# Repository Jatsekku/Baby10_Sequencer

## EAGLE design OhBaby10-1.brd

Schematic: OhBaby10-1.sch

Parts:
C1, C1S, C2, C2S, C3, C3S, C4, C4S, C5, C5S, C6, C6S, C7, C7S, C8, C8S, C9, C9S, C10, C10S, C11, C11S, C12, C12S, C20: C-EUC0805; C0805
C1P: CPOL-EU153CLV-0405; 153CLV-0405
C2P: C-EUC0805K; C0805K
C3P: 470nF; C0805
CV_OUT: JACK3.5; JACK_FANCY
D1P: SM4001; MELF-MLL41_DO213AB
DSA: CPOL-EU153CLV-0405; 153CLV-0405
EXT_CLK_IN, EXT_CLK_IN1: JACK3.5; JACK_FANCY
F1: FUSEB; 0805
IC1, IC2, IC3, IC4, IC5, IC6, IC7, IC8, IC9, IC10, IC11, IC12: TTP223-BA6; SOT95P285X126-6N
IC13, IC14, IC17: 74HC08D; SO14
IC15: 4017D; SO16
IC16: 74HC32D; SO14
IC18: IC_TD62783-SO-18W; SO-18L
IC19: NE555D; SO08
IC20: REG1117; SOT223
LED1, LED2, LED3, LED4, LED5, LED6, LED7, LED8, LED9, LED10, LED11, LED12: LED_3PIN; LED_3PIN_SMD
OUT_S1, OUT_S2, OUT_S3, OUT_S4, OUT_S5, OUT_S6, OUT_S7, OUT_S8: JACK3.5; JACK_FANCY
POT_S1, POT_S2, POT_S3, POT_S4, POT_S5, POT_S6, POT_S7, POT_S8: V_POT; POT_FANCY
POWER: IDC10; ML10
R1, R1Q, R2Q, R3Q, R3Q1, R4Q, R5Q, R8Q, R9Q: R-EU_R1206; R1206
R1L, R2L, R3L, R4L, R5L, R6L, R6Q, R7L, R7Q, R8L, R9L, R10L, R10Q, R11L, R12L: R-EU_R0805; R0805
TP1, TP2, TP3, TP4, TP5, TP6, TP7, TP8, TP10, TP11, TP12, TP13: TOUCH_PAD; TOUCH_PAD_8X8
U$1: JST_2MM_10P
U$2, U$7, U$8, U$9, U$10, U$11, U$12, U$13, U$14, U$15, U$16, U$17, U$18, U$19, U$20, U$21, U$23, U$24, U$25, U$26: SP_SMD; SINGLE_PAD_SMD
U$4: JST_2MM_9P
U$5: JST_2MM_2P
U$6: V_POT; POT_FANCY
U$22: JST_2MM_6P
Z1, Z2, Z8, Z9: R-EU_R1206; R1206
Z3, Z4, Z5, Z6, Z7, Z10: R-EU_R2010; R2010

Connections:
555_CLK: IC19.3 (Q), U$22.P$2 (2)
555_VCC: C20.1, IC19.4 (R), IC19.8 (V+), U$5.P$2 (2), Z9.1
4017_Q0: IC13.12 (I0), IC15.3 (Q0), R1Q.1
4017_Q1: IC13.1 (I0), IC15.2 (Q1), R2Q.1, U$4.P$8 (8)
4017_Q2: IC14.1 (I0), IC15.4 (Q2), R3Q.1, U$4.P$7 (7)
4017_Q3: IC15.7 (Q3), R4Q.1, U$4.P$4 (4), Z5.1
4017_Q4: IC13.9 (I0), IC15.10 (Q4), R5Q.1, U$4.P$3 (3)
4017_Q5: IC13.4 (I0), IC15.1 (Q5), R6Q.2, U$4.P$9 (9)
4017_Q6: IC14.4 (I0), IC15.5 (Q6), R7Q.2, U$4.P$6 (6)
4017_Q7: IC15.6 (Q7), R8Q.1, U$4.P$5 (5), Z4.1
4017_Q8: IC15.9 (Q8), U$4.P$2 (2)
+12V_PWR: D1P.C, F1.1, POWER.9, POWER.10
CLK_SUM: IC15.14 (CLK), IC16.6 (O), R10Q.1
GND: C1.2, C1P.-, C1S.2, C2.2, C2P.2, C2S.2, C3.2, C3P.2, C3S.2, C4.2, C4S.2, C5.2, C5S.2, C6.2, C6S.2, C7.2, C7S.2, C8.2, C8S.2, C9.2, C9S.2, C10.2, C10S.2, C11.2, C11S.2, C12.2, C12S.2, C20.2, D1P.A, DSA.-, IC1.2 (VSS), IC1.4 (AHLB), IC2.2 (VSS), IC2.4 (AHLB), IC3.2 (VSS), IC3.4 (AHLB), IC4.2 (VSS), IC4.4 (AHLB), IC5.2 (VSS), IC5.4 (AHLB), IC6.2 (VSS), IC6.4 (AHLB), IC7.2 (VSS), IC7.4 (AHLB), IC8.2 (VSS), IC8.4 (AHLB), IC9.2 (VSS), IC9.4 (AHLB), IC9.6 (TOG), IC10.2 (VSS), IC10.4 (AHLB), IC10.6 (TOG), IC11.2 (VSS), IC11.4 (AHLB), IC12.2 (VSS), IC12.4 (AHLB), IC13.7 (GND), IC14.7 (GND), IC15.8 (VSS), IC15.13 (ENA), IC16.7 (GND), IC17.7 (GND), IC18.10 (VS), IC19.1 (GND), IC20.1 (GND), LED1.P$1 (C), LED2.P$1 (C), LED3.P$1 (C), LED4.P$1 (C), LED5.P$1 (C), LED6.P$1 (C), LED7.P$1 (C), LED8.P$1 (C), LED9.P$1 (C), LED10.P$1 (C), LED11.P$1 (C), LED12.P$1 (C), POWER.3, POWER.4, POWER.5, POWER.6, POWER.7, POWER.8, R3Q1.1, R3Q1.2, U$1.P$9 (9), U$22.P$6 (6)
INT/EXT_CLK: IC17.4 (I0), U$22.P$4 (4)
INT/EXT_RST: IC17.1 (I0), U$22.P$3 (3)
KEY1: IC1.1 (Q), IC13.13 (I1), R1L.1
KEY2: IC2.1 (Q), IC13.2 (I1), R2L.1
KEY3: IC3.1 (Q), IC14.2 (I1), R3L.1
KEY4: IC4.1 (Q), R4L.1, Z7.1
KEY5: IC5.1 (Q), R5L.1, Z8.1
KEY6: IC6.1 (Q), IC13.5 (I1), R6L.1
KEY7: IC7.1 (Q), IC14.5 (I1), R7L.1
KEY8: IC8.1 (Q), R8L.1, Z6.1
KEY11: IC11.1 (Q), IC17.5 (I1), R11L.2
MAN_CLK: IC10.1 (Q), IC16.4 (I0), R10L.2
MAN_RST: IC9.1 (Q), IC16.1 (I0), R9L.2
unnamed: DSA.+, IC19.2 (TR), IC19.6 (THR), R1.1
unnamed: C10S.1, IC10.3 (I), TP11.P$1
unnamed: IC19.7 (DIS), R1.2, U$5.P$1 (1)
unnamed: LED9.P$2 (AR), R10L.1
unnamed: C1S.1, IC1.3 (I), TP1.P$1
unnamed: C11S.1, IC11.3 (I), TP12.P$1
unnamed: LED12.P$2 (AR), R11L.1
unnamed: C9S.1, IC9.3 (I), TP13.P$1
unnamed: LED1.P$2 (AR), R1Q.2
unnamed: C5S.1, IC5.3 (I), TP5.P$1
unnamed: IC16.5 (I1), U$26.P$1
unnamed: LED10.P$2 (AR), R9L.1
unnamed: LED1.P$3 (AG), R1L.2
unnamed: LED2.P$2 (AR), R2Q.2
unnamed: LED9.P$3 (AG), R10Q.2
unnamed: LED2.P$3 (AG), R2L.2
unnamed: C2S.1, IC2.3 (I), TP2.P$1
unnamed: IC16.2 (I1), U$23.P$1
unnamed: LED3.P$2 (AR), R3Q.2
unnamed: LED3.P$3 (AG), R3L.2
unnamed: C12S.1, IC12.3 (I), TP10.P$1
unnamed: LED4.P$2 (AR), R4Q.2
unnamed: LED11.P$2 (AR), R12L.1
unnamed: LED4.P$3 (AG), R4L.2
unnamed: LED5.P$2 (AR), R5Q.2
unnamed: C3S.1, IC3.3 (I), TP3.P$1
unnamed: LED5.P$3 (AG), R5L.2
unnamed: LED6.P$2 (AR), R6Q.1
unnamed: LED6.P$3 (AG), R6L.2
unnamed: LED7.P$2 (AR), R7Q.1
unnamed: C4S.1, IC4.3 (I), TP4.P$1
unnamed: LED7.P$3 (AG), R7L.2
unnamed: LED8.P$2 (AR), R8Q.2
unnamed: IC17.3 (O), U$24.P$1
unnamed: IC17.6 (O), U$25.P$1
unnamed: IC17.2 (I1), Z10.2
unnamed: LED8.P$3 (AG), R8L.2
unnamed: IC18.14 (OUT5), U$1.P$5 (5)
unnamed: IC18.13 (OUT6), U$1.P$6 (6)
unnamed: IC18.12 (OUT7), U$1.P$7 (7)
unnamed: IC18.11 (OUT8), U$1.P$8 (8)
unnamed: IC18.15 (OUT4), U$1.P$4 (4)
unnamed: IC18.16 (OUT3), U$1.P$3 (3)
unnamed: C6S.1, IC6.3 (I), TP6.P$1
unnamed: IC18.17 (OUT2), U$1.P$2 (2)
unnamed: IC18.18 (OUT1), U$1.P$1 (1)
unnamed: LED10.P$3 (AG), R9Q.1
unnamed: C1P.+, C2P.1, F1.2, IC20.3 (VIN)
unnamed: C7S.1, IC7.3 (I), TP7.P$1
unnamed: IC13.11 (O), U$7.P$1
unnamed: IC13.3 (O), U$8.P$1
unnamed: C8S.1, IC8.3 (I), TP8.P$1
unnamed: IC14.3 (O), U$9.P$1
unnamed: IC14.11 (O), U$10.P$1
unnamed: IC13.8 (O), U$11.P$1
unnamed: IC13.6 (O), U$12.P$1
unnamed: IC14.6 (O), U$13.P$1
unnamed: IC14.8 (O), U$14.P$1
unnamed: IC14.9 (I0), Z4.2
unnamed: IC14.10 (I1), Z6.2
unnamed: IC14.12 (I0), Z5.2
unnamed: IC14.13 (I1), Z7.2
unnamed: C5.1, IC5.5 (VDD), IC5.6 (TOG), Z1.1
unnamed: C6.1, IC6.5 (VDD), IC6.6 (TOG), Z2.1
unnamed: C7.1, IC7.5 (VDD), IC7.6 (TOG), Z3.1
unnamed: IC13.10 (I1), Z8.2
unnamed: IC18.1 (IN1), U$2.P$1
unnamed: IC18.2 (IN2), U$15.P$1
unnamed: IC18.3 (IN3), U$16.P$1
unnamed: IC18.4 (IN4), U$17.P$1
unnamed: IC18.5 (IN5), U$18.P$1
unnamed: IC18.6 (IN6), U$19.P$1
unnamed: IC18.7 (IN7), U$20.P$1
unnamed: IC18.8 (IN8), U$21.P$1
RST_SEL: U$4.P$1 (1), U$22.P$1 (1)
RST_SUM: IC15.15 (RES), IC16.3 (O), R9Q.2
RS_EXT_ENABLE: IC12.1 (Q), R12L.2, Z10.1
VCC: C1.1, C2.1, C3.1, C3P.1, C4.1, C8.1, C9.1, C10.1, C11.1, C12.1, IC1.5 (VDD), IC1.6 (TOG), IC2.5 (VDD), IC2.6 (TOG), IC3.5 (VDD), IC3.6 (TOG), IC4.5 (VDD), IC4.6 (TOG), IC8.5 (VDD), IC8.6 (TOG), IC9.5 (VDD), IC10.5 (VDD), IC11.5 (VDD), IC11.6 (TOG), IC12.5 (VDD), IC12.6 (TOG), IC13.14 (VCC), IC14.14 (VCC), IC15.16 (VDD), IC16.14 (VCC), IC17.14 (VCC), IC18.9 (GND), IC20.2 (VOUT), Z1.2, Z2.2, Z3.2, Z9.2

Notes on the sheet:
Keypad
Clk_Internal
Clk_Ext_In
Clk_Manual
Clk_Control
Rst_Manual
Rst_Ext_In
Rst_Control
Clock
Reset

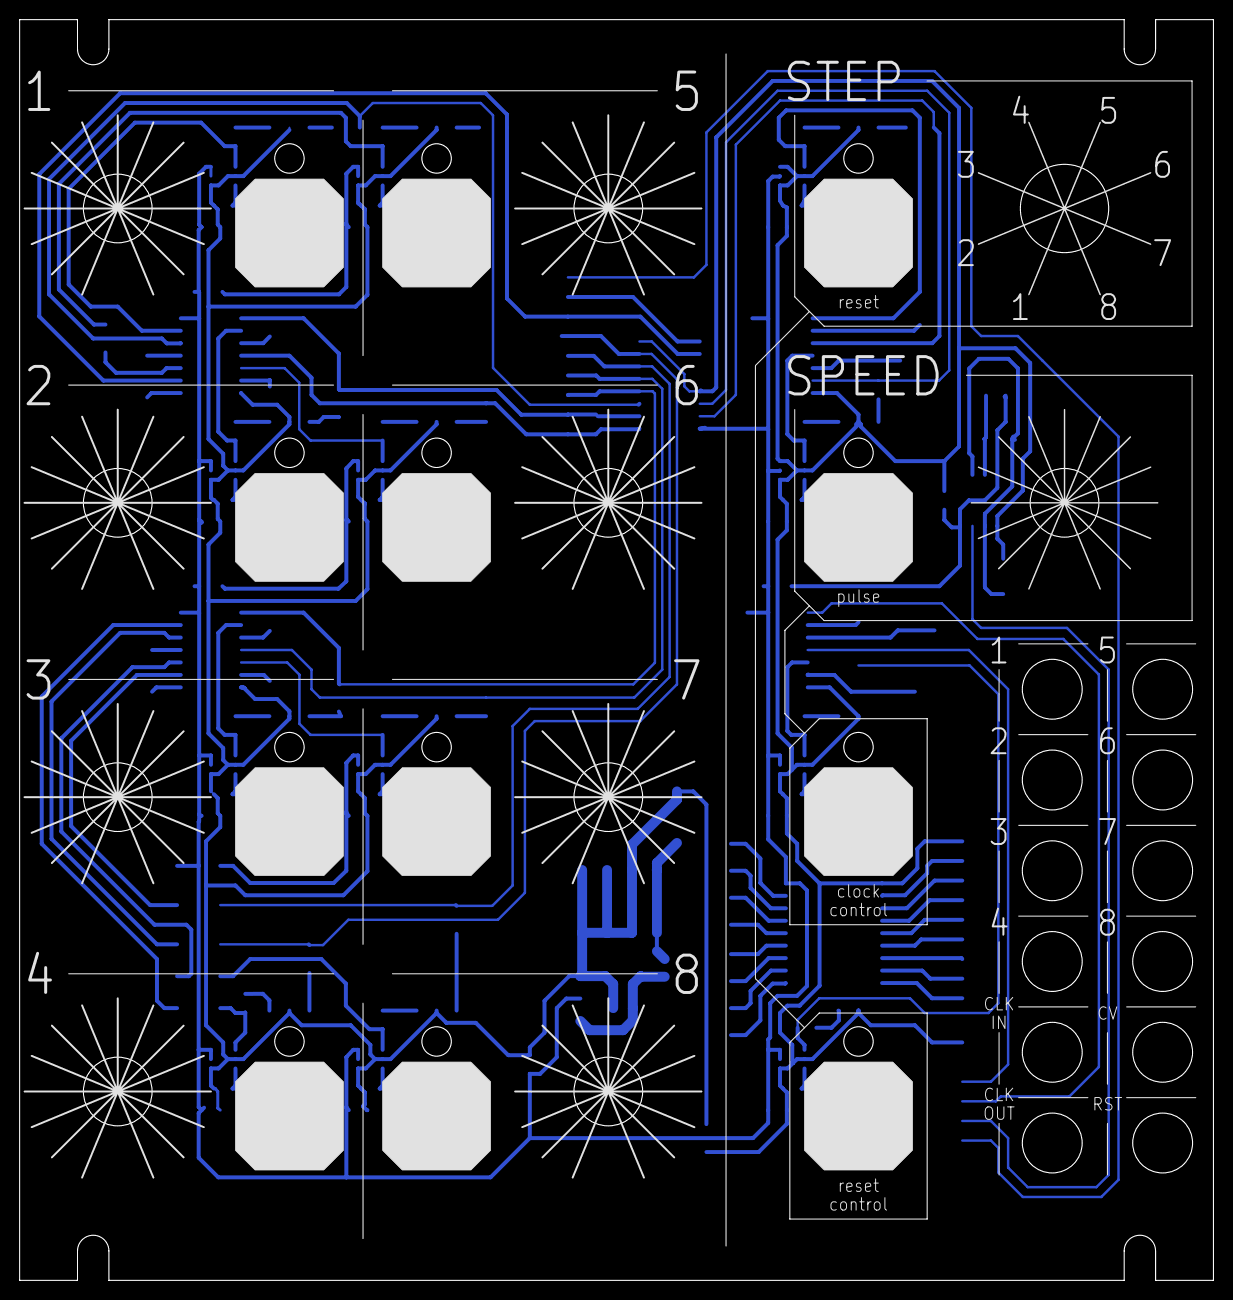
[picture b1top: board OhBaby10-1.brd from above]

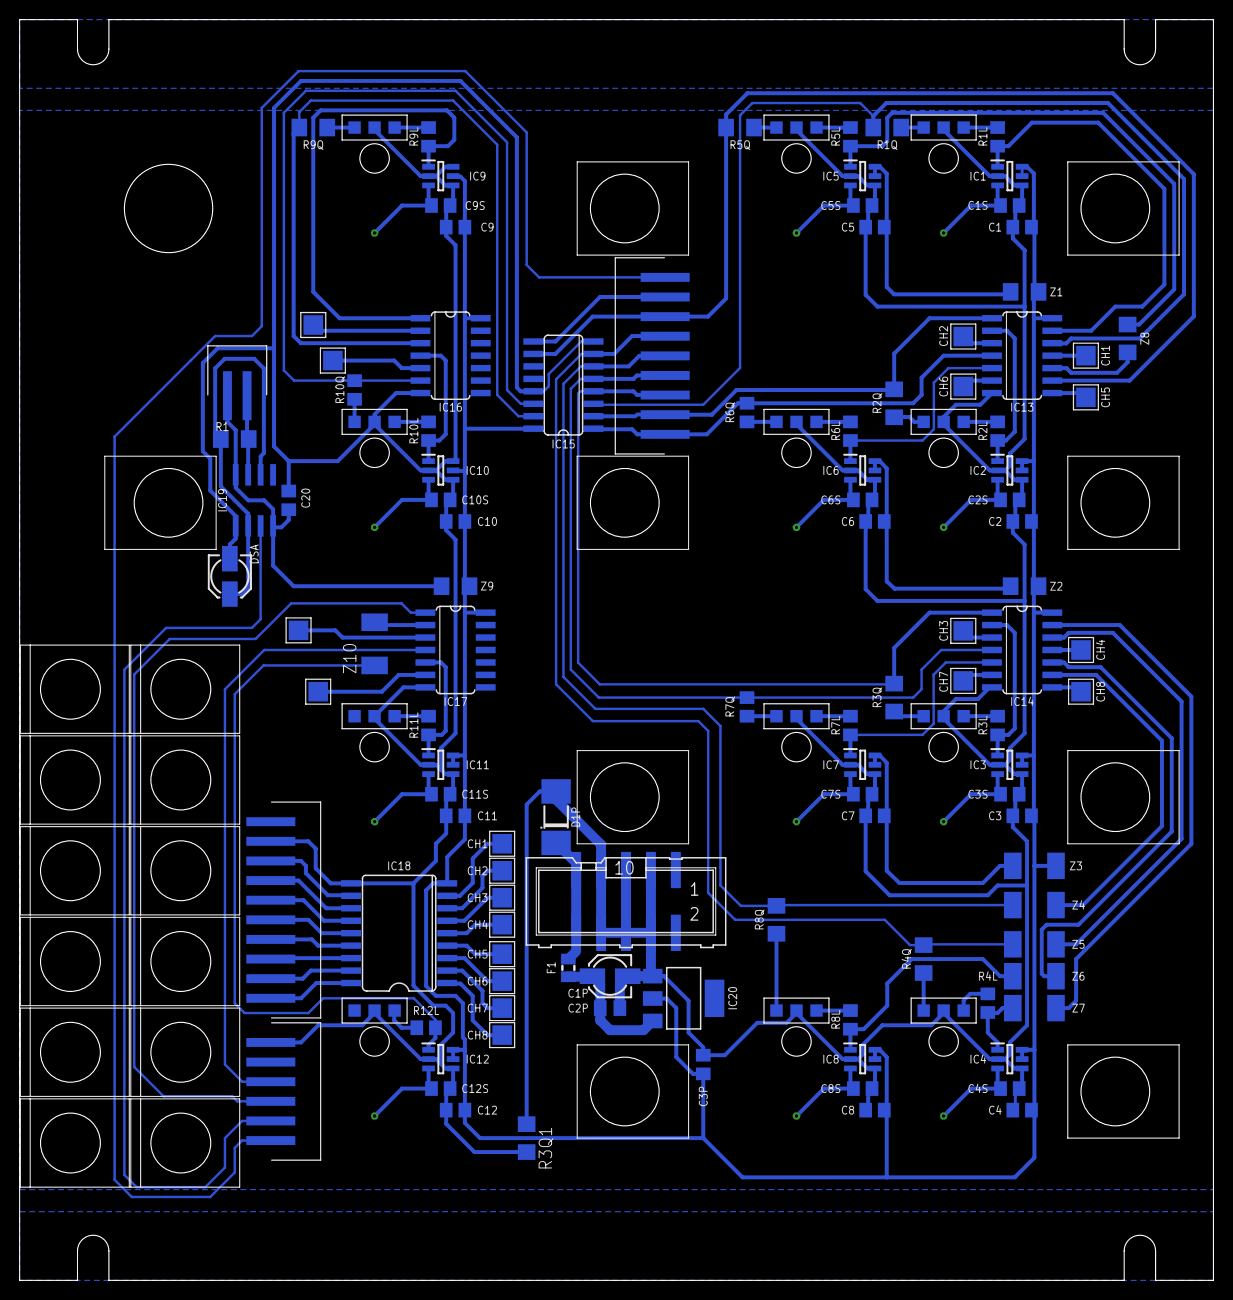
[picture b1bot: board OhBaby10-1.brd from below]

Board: 2 copper layers, 121.7 x 128.5 mm, 155 parts (143 on the bottom side), 105 nets.

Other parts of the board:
U$3: JACK3.5; JACK_FANCY

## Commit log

2020-01-07 Almost done

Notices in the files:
parts and their libraries:
m-pad-2.1: License : GNU General Public License version 2 (see bottom)
